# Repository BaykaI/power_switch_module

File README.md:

# power_switch_module
Разработана плата модуля ключа питания для устройств PCIe.
ТЗ:
Входное питание стандарта ATX 12В.;
Питание со входного разъёма ATX-PCIe-8pin;
Управление через интерфейс RS485 по протоколу ModBus;
Для подключения управления использовались разъёмы 4P4C в количестве 2 шт., соединённые параллельно для объединения нескольких модулей в цепочку;
Терминирование RS485 через джампер (3pin, дабы не потерять сам джампер);
измерение тока нагрузки;
измерение напряжения на входе и выходе;
Входной разъём типа Male, выходной - Female.
В данной задаче делалсь структурная и принципиальная схемы, топология.

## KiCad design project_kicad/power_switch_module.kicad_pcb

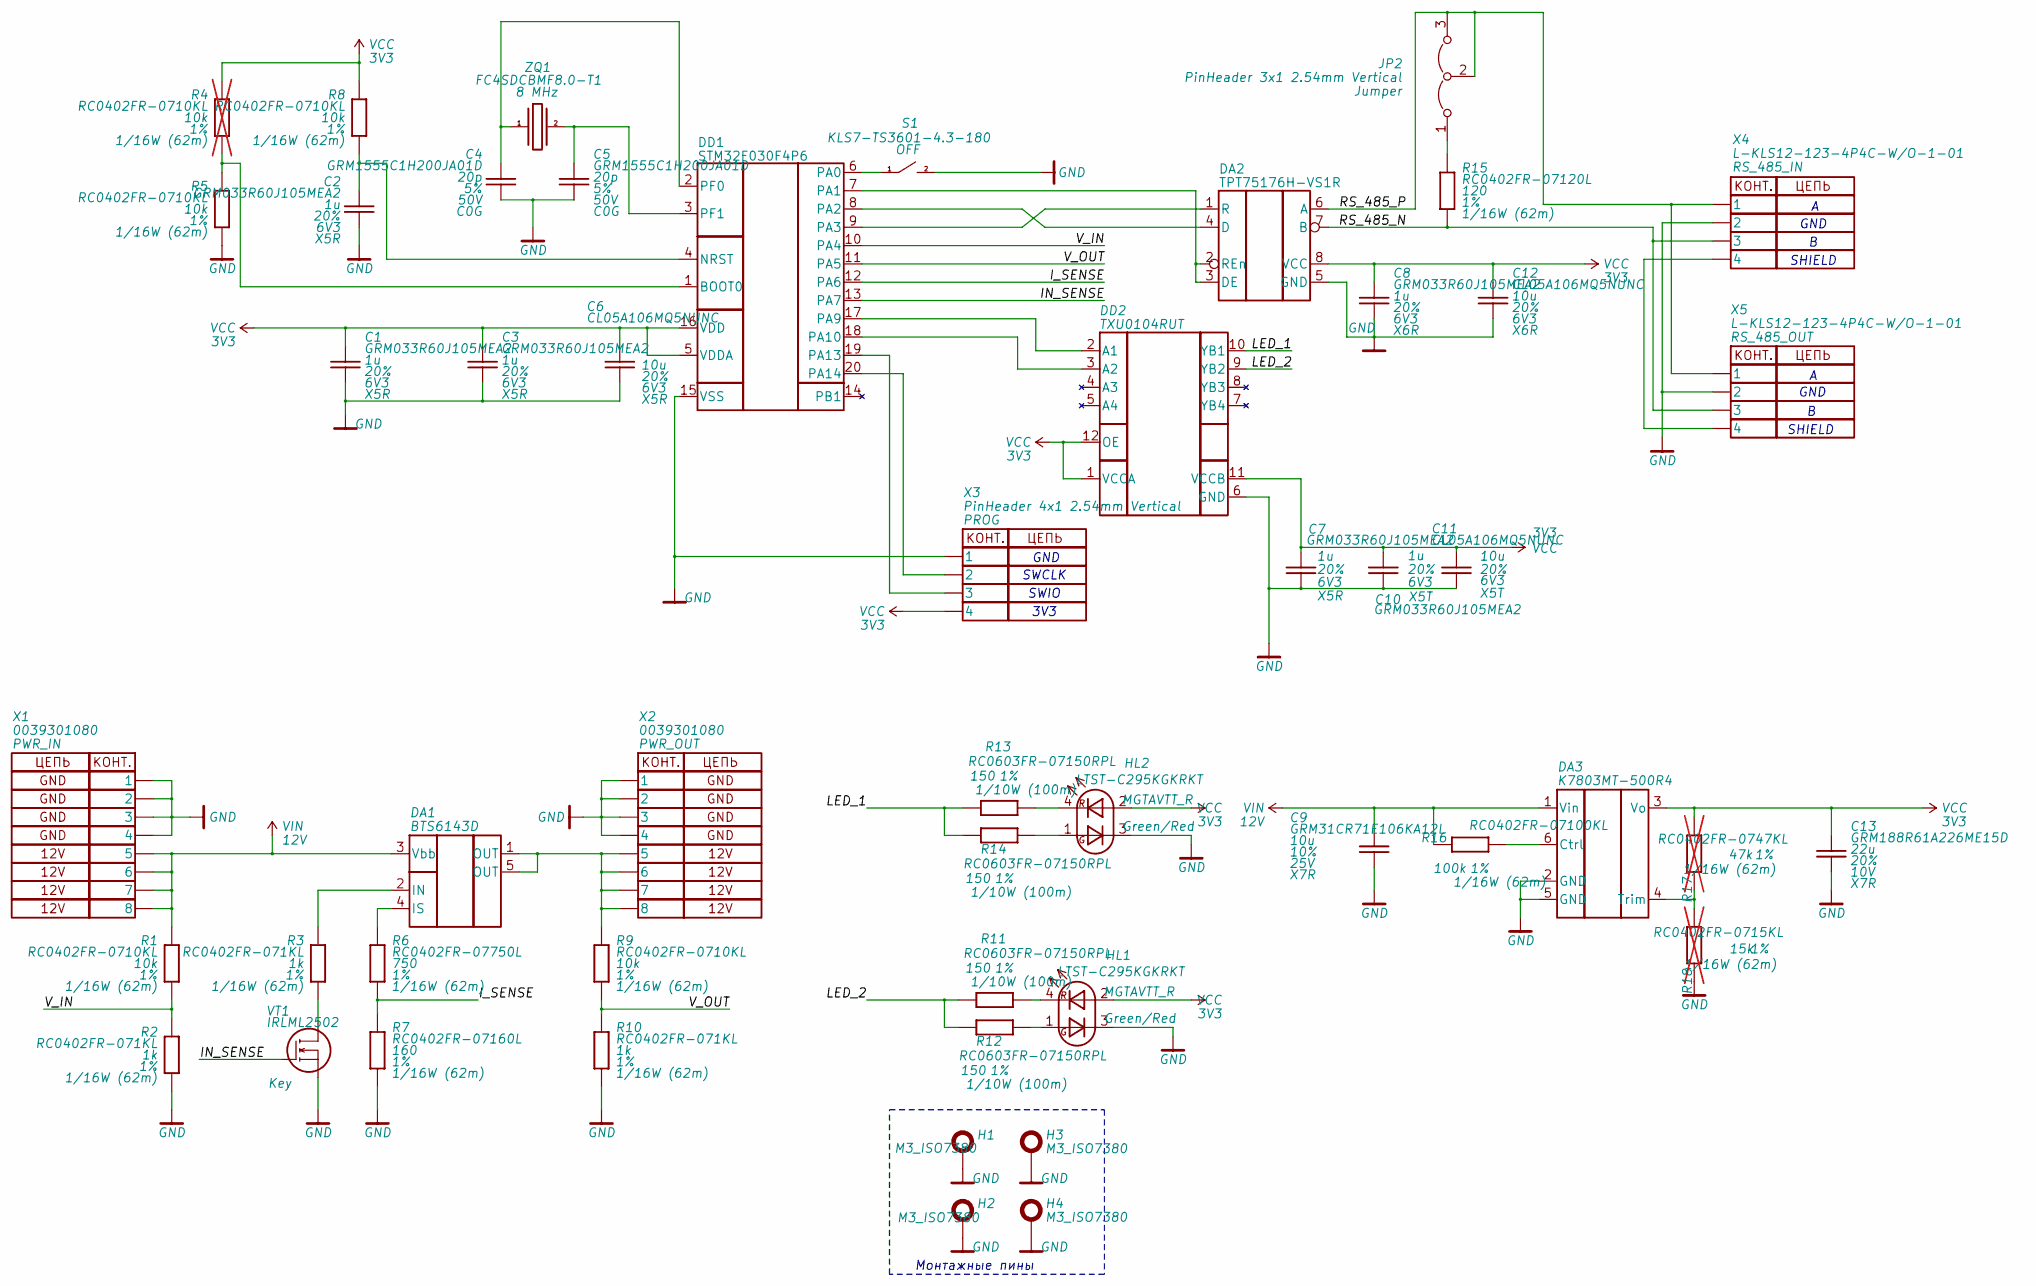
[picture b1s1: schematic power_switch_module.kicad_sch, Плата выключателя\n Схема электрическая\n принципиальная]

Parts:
C1, C2, C3, C7, C8, C10: GRM033R60J105MEA2; C_0201_0603Metric; Tolerance 20%
C4, C5: GRM1555C1H200JA01D; C_0201_0603Metric; Tolerance 5%
C6, C11, C12: CL05A106MQ5NUNC; C_0402_1005Metric; Tolerance 20%
C9: GRM31CR71E106KA12L; C_1206_3216Metric; Tolerance 10%
C13: GRM188R61A226ME15D; C_0201_0603Metric; Tolerance 20%
DA1: BTS6143D; TO-252-4
DA2: TPT75176H-VS1R; MSOP-8_3x3mm_P0.65mm
DA3: K7803MT-500R4; K7803MT-500R4_1
DD1: STM32F030F4P6; TSSOP-20_4.4x6.5mm_P0.65mm
DD2: TXU0104RUT; UQFN-12
H1, H2, H3, H4: M3_ISO7380; MountingHole_3.2mm_M3_ISO7380_Pad
HL1, HL2: LTST-C295KGKRKT; LTST-C295
JP2: PinHeader 3x1 2.54mm Vertical; PinHeader_1x03_P2.54mm_Vertical
R1, R5, R8, R9: RC0402FR-0710KL; R_0402_1005Metric; Tolerance 1%
R2, R3, R10: RC0402FR-071KL; R_0402_1005Metric; Tolerance 1%
R4: RC0402FR-0710KL; R_0402_1005Metric; Tolerance 1%; not fitted
R6: RC0402FR-07750L; R_0402_1005Metric; Tolerance 1%
R7: RC0402FR-07160L; R_0402_1005Metric; Tolerance 1%
R11, R12, R13, R14: RC0603FR-07150RPL; R_0603_1608Metric; Tolerance 1%
R15: RC0402FR-07120L; R_0402_1005Metric; Tolerance 1%
R16: RC0402FR-07100KL; R_0402_1005Metric; Tolerance 1%
R17: RC0402FR-0747KL; R_0402_1005Metric; Tolerance 1%; not fitted
R18: RC0402FR-0715KL; R_0402_1005Metric; Tolerance 1%; not fitted
S1: KLS7-TS3601-4.3-180; SW_Tactile_SPST_NO_Straight_CK_PTS636Sx25SMTRLFS
VT1: IRLML2502; SOT-23
X1, X2: 0039301080; Molex_Mini-Fit_Jr_5569-08A2_2x04_P4.20mm_Horizontal
X3: PinHeader 4x1 2.54mm Vertical; PinHeader_1x04_P2.54mm_Vertical
X4, X5: L-KLS12-123-4P4C-W/O-1-01; RJ9_Evercom_5301-440xxx_Horizontal
ZQ1: FC4SDCBMF8.0-T1; Crystal_SMD_HC49-SD

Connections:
/IN_SENSE: DD1.13 (PA7), VT1.1
/I_SENSE: DD1.12 (PA6), R6.1, R7.2
/LED_1: DD2.10 (YB1), R13.2, R14.2
/LED_2: DD2.9 (YB2), R11.2, R12.2
/RS_485_N: DA2.7 (B), R15.1, X4.3, X5.3
/RS_485_P: DA2.6 (A), JP2.2 (C), JP2.3 (B), X4.1, X5.1
/V_IN: DD1.10 (PA4), R1.1, R2.2
/V_OUT: DD1.11 (PA5), R9.1, R10.2
GND: C1.2, C2.2, C3.2, C4.2, C5.2, C6.2, C7.2, C8.2, C9.2, C10.2, C11.2, C12.2, C13.2, DA2.5 (GND), DA3.2 (GND), DA3.5 (GND), DD1.15 (VSS), DD2.6 (GND), H1.1, H2.1, H3.1, H4.1, HL1.3 (K1), HL2.3 (K1), R2.1, R5.1, R7.1, R10.1, R18.2, S1.2, VT1.2, X1.1, X1.2, X1.3, X1.4, X2.1, X2.2, X2.3, X2.4, X3.1, X4.2, X5.2; also elsewhere on the board
unnamed: DA1.2 (IN), R3.2
unnamed: DA1.4 (IS), R6.2
unnamed 11: DA1.1 (OUT), DA1.5 (OUT), R9.2, X2.5, X2.6, X2.7, X2.8; also elsewhere on the board
unnamed: DA2.4 (D), DD1.8 (PA2)
unnamed: DA2.2 (REn), DA2.3 (DE), DD1.7 (PA1)
unnamed: DA2.1 (R), DD1.9 (PA3)
unnamed: DA3.6 (Ctrl), R16.1
unnamed: DA3.4 (Trim), R17.2, R18.1
unnamed: DD1.1 (BOOT0), R4.1, R5.2
unnamed: C2.1, DD1.4 (NRST), R8.1
unnamed: DD1.6 (PA0), S1.1
unnamed: DD1.17 (PA9), DD2.2 (A1)
unnamed: DD1.18 (PA10), DD2.3 (A2)
unnamed: DD1.19 (PA13), X3.3
unnamed: DD1.20 (PA14), X3.2
unnamed: C4.1, DD1.2 (PF0), ZQ1.1
unnamed: C5.1, DD1.3 (PF1), ZQ1.2
unnamed: HL1.1 (A1), R12.1
unnamed: HL1.4 (K2), R11.1
unnamed: HL2.1 (A1), R14.1
unnamed: HL2.4 (K2), R13.1
unnamed: JP2.1 (A), R15.2
unnamed: R3.1, VT1.3
unnamed: X4.4, X5.4
VCC: C1.1, C3.1, C6.1, C7.1, C8.1, C10.1, C11.1, C12.1, C13.1, DA2.8 (VCC), DA3.3 (Vo), DD1.5 (VDDA), DD1.16 (VDD), DD2.1 (VCCA), DD2.11 (VCCB), DD2.12 (OE), HL1.2 (A2), HL2.2 (A2), R4.2, R8.2, R17.1, X3.4
VIN: C9.1, DA1.3 (Vbb), DA3.1 (Vin), R1.2, R16.2, X1.5, X1.6, X1.7, X1.8; also elsewhere on the board

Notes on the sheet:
SHIELD
GND
3V3
Монтажные пины
SWIO
SWCLK

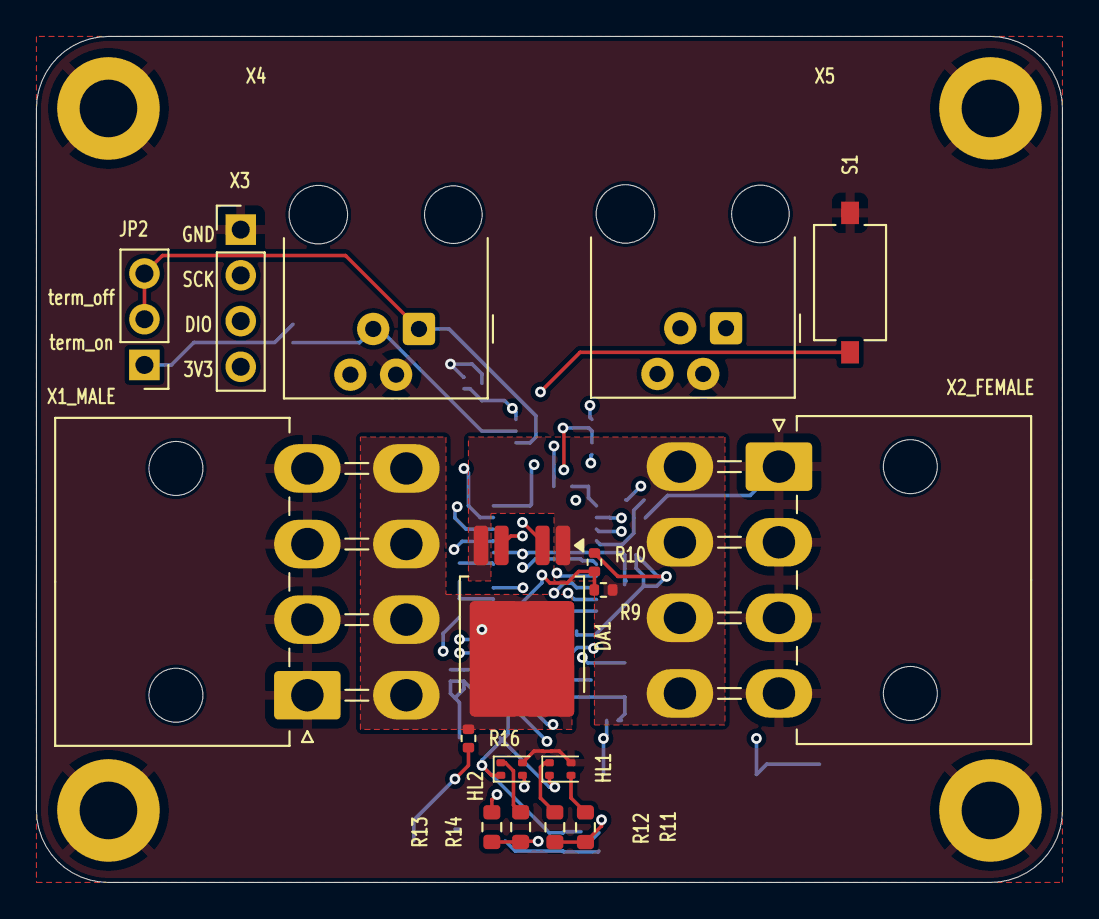
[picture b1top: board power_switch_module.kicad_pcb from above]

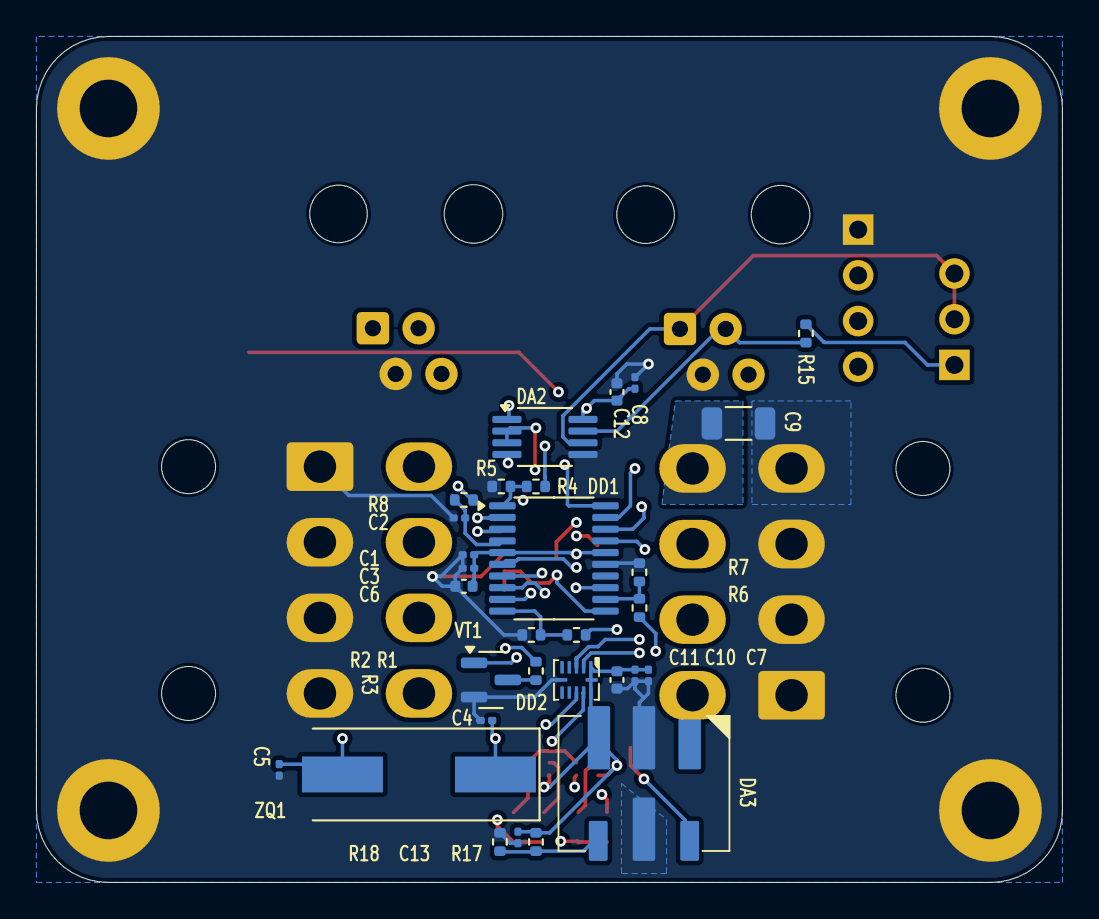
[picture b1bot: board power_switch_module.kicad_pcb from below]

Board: 4 copper layers, 57.0 x 47.0 mm, 51 parts (30 on the bottom side), 35 nets.

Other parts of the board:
X1_MALE, X2_FEMALE: 0039301080; Molex_Mini-Fit_Jr_5569-08A2_2x04_P4.20mm_Horizontal

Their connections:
GND: X1_MALE.1, X1_MALE.2, X1_MALE.3, X1_MALE.4, X2_FEMALE.1, X2_FEMALE.2, X2_FEMALE.3, X2_FEMALE.4; also elsewhere on the board
unnamed 11: X2_FEMALE.5, X2_FEMALE.6, X2_FEMALE.7, X2_FEMALE.8; also elsewhere on the board
VIN: X1_MALE.5, X1_MALE.6, X1_MALE.7, X1_MALE.8; also elsewhere on the board

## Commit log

2025-07-12 Start
